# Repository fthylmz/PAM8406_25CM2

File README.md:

# PAM8406_25CM2
It's a stereo amplifier, nothing's special about this project, it's partly based on [reference design](http://www.mouser.com/ds/2/115/PAM8406-247303.pdf).

## DETAILS

1. All SMD components are 1206 sized regardless of their advantages over audio designs.
2. Input capacitor should be chosen something over 470uF/6V but the footprint I used has lead size 5mm.
3. The coil I used in LPF part of circuit is from CoilCraft, its product code is JA4575-BL.
4. Etc.

I'm not an EE, or had any educations about this topic, it's just my hobby project I consider to use in my future audio projects.

## TO-DO
- [ ] Make room for bigger decoupling caps and include multi pads for variable input capacitor types \(5mm, 8mm, etc.\) to the design.
- [ ] \(Optional\) Add a boost converter to the circuit.
- [ ] Use more common coils in LPF.
- [X] LPF in front of AVDD may be needed, if it's not just include 0R resistors in place.
- [ ] Make optimizations at audio input part.
- [ ] \(Optional\) Make it **perfect** :punch:.

## TESTS
Never tested but I'm confident. :boom:

## LICENSE

© 2017 Fatih YILMAZ

This project is licensed under the [TAPR Open Hardware License V 1.0](www.tapr.org/OHL) and commercial use is acceptable - see the [LICENSE.txt](LICENSE.txt) file for details.

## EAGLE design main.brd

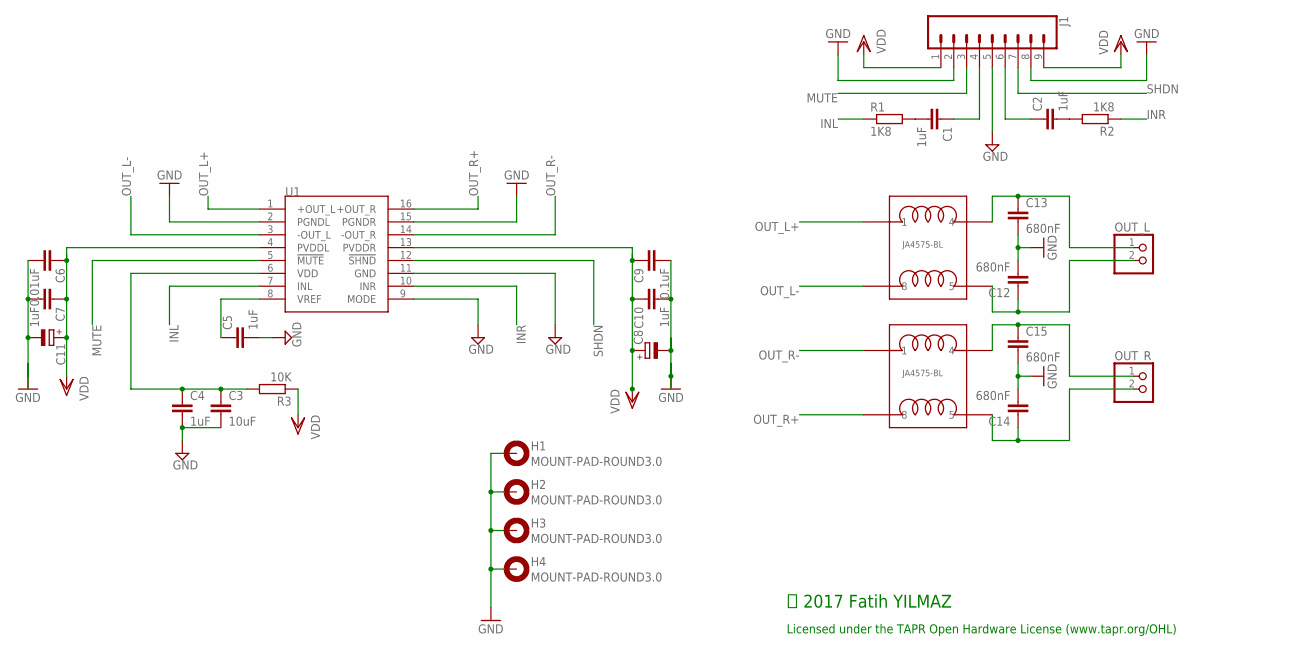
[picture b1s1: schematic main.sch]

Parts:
C1, C2: 1uF; C1206; MPN C0603C105K4PACTU
C3: 10uF; C1206
C4, C5, C7, C10: 1uF; C1206
C6: 0.01uF; C1206
C8, C11: CPOL-EUE3.5-8; E3,5-8
C9: 0.1uF; C1206
C12, C13, C14, C15: 680nF; C050-045X075
H1, H2, H3, H4: MOUNT-PAD-ROUND3.0; 3,0-PAD
J1: CONN_09NO_SILK; 1X09_NO_SILK
LEFT_COIL: JA4575-BL
OUT_L: PINHD-1X2; 1X02
OUT_R: PINHD-1X2; 1X02
R1, R2: 1K8; R1206
R3: 10K; R1206
RIGHT_COIL: JA4575-BL
U1: PAM8403; SOP-16

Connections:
AVDD: C3.1, C4.1, R3.2, U1.6 (VDD)
GND: C3.2, C4.2, C5.2, C6.2, C7.2, C8.-, C9.2, C10.2, C11.-, C12.2, C13.2, C14.2, C15.2, H1.B3,0, H2.B3,0, H3.B3,0, H4.B3,0, J1.2, J1.5, J1.8, U1.2 (PGNDL), U1.9 (MODE), U1.11 (GND), U1.15 (PGNDR)
INL: R1.1, U1.7 (INL)
INR: R2.1, U1.10 (INR)
MUTE: J1.3, U1.5 (!MUTE)
unnamed: C1.2, R1.2
unnamed: C2.2, R2.2
unnamed: C1.1, J1.4
unnamed: C13.1, LEFT_COIL.4, OUT_L.1
unnamed: C2.1, J1.6
unnamed: C15.1, OUT_R.1, RIGHT_COIL.4
unnamed: C14.1, OUT_R.2, RIGHT_COIL.5
unnamed: C12.1, LEFT_COIL.5, OUT_L.2
OUT_L+: LEFT_COIL.1, U1.1 (+OUT_L)
OUT_L-: LEFT_COIL.8, U1.3 (-OUT_L)
OUT_R+: RIGHT_COIL.8, U1.16 (+OUT_R)
OUT_R-: RIGHT_COIL.1, U1.14 (-OUT_R)
SHDN: J1.7, U1.12 (!SHND)
VDD: C6.1, C7.1, C8.+, C9.1, C10.1, C11.+, J1.1, J1.9, R3.1, U1.4 (PVDDL), U1.13 (PVDDR)
VREF: C5.1, U1.8 (VREF)

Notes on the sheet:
Licensed under the TAPR Open Hardware License (www.tapr.org/OHL)
Ⓒ 2017 Fatih YILMAZ

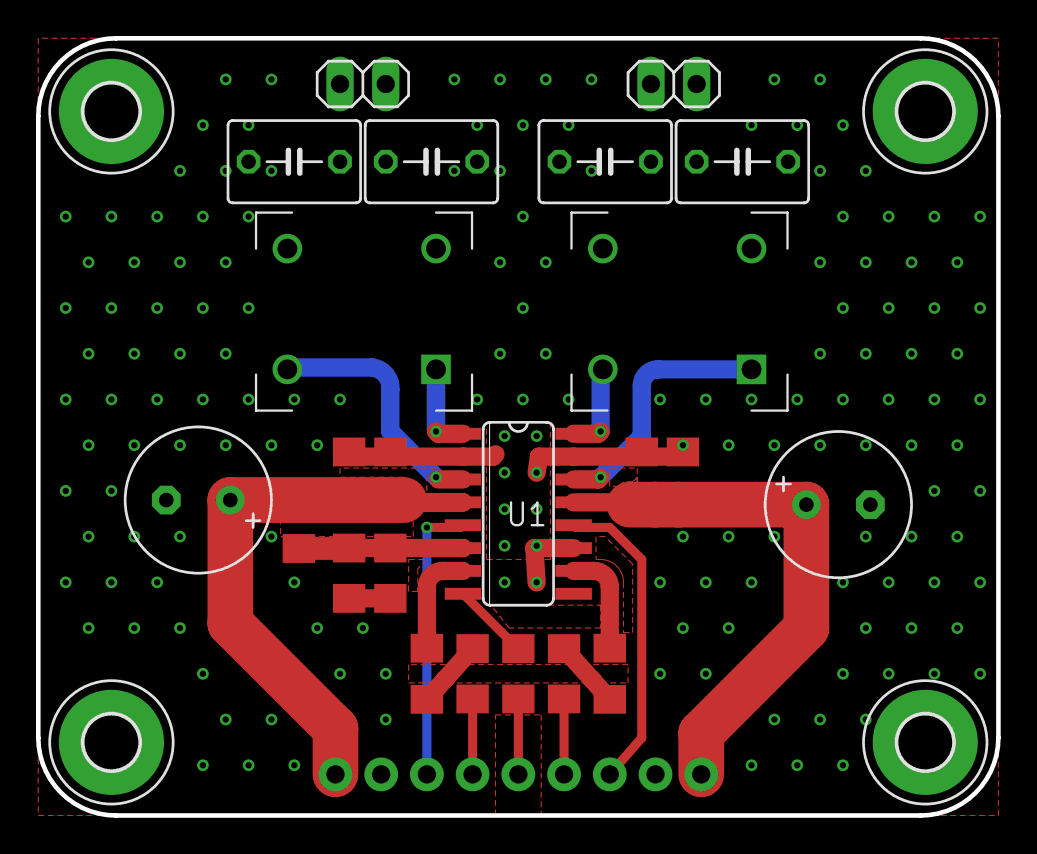
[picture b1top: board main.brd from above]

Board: 2 copper layers, 53.3 x 43.2 mm, 28 parts (0 on the bottom side), 20 nets.

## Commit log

2017-10-12 rev 2.0
    board size's reduced, main bypass cap's size and value has changed.
2017-11-01 New board design
2017-11-01 edited layer settings

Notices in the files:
main.brd:
LICENSED UNDER THE TAPR OHL V 1.0
parts and their libraries:
SparkFun-Connectors: Licensing: Creative Commons ShareAlike 4.0 International - https://creativecommons.org/licenses/by-sa/4.0
